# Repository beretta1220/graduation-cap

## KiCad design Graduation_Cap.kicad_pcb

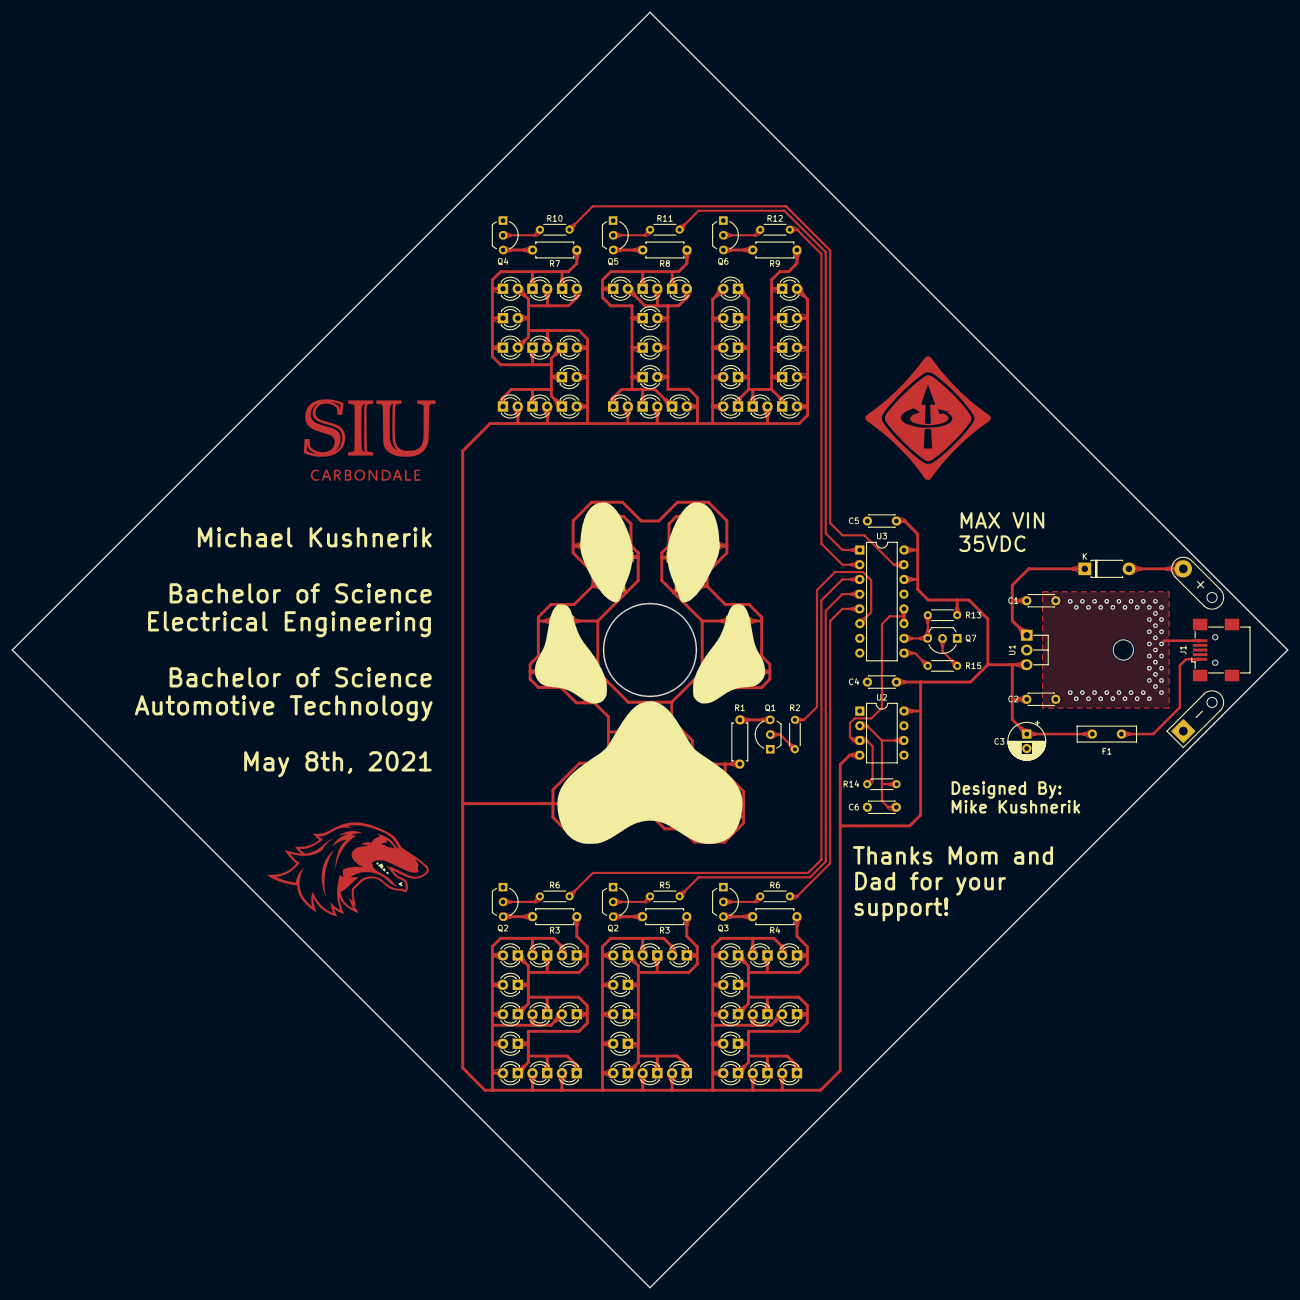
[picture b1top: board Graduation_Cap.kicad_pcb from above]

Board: 2 copper layers, 220.0 x 220.0 mm, 129 parts (0 on the bottom side), 37 nets.

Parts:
C1, C2, C4, C5, C6: 0.1uF; C_Disc_D4.3mm_W1.9mm_P5.00mm
C3: 10uF; CP_Radial_D6.3mm_P2.50mm
D1: P1; LED_D3.0mm
D2: P2; LED_D3.0mm
D3: P3; LED_D3.0mm
D4: P4; LED_D3.0mm
D5: P5; LED_D3.0mm
D6: P6; LED_D3.0mm
D7: P7; LED_D3.0mm
D8: P8; LED_D3.0mm
D9: P9; LED_D3.0mm
D10: P10; LED_D3.0mm
D11: P11; LED_D3.0mm
D12: P12; LED_D3.0mm
D13: P13; LED_D3.0mm
D14: P14; LED_D3.0mm
D15: P15; LED_D3.0mm
D16: P16; LED_D3.0mm
D17: P17; LED_D3.0mm
D18: P18; LED_D3.0mm
D19: P19; LED_D3.0mm
D20: P20; LED_D3.0mm
D21: P21; LED_D3.0mm
D22: P22; LED_D3.0mm
D23: P23; LED_D3.0mm
D24: P24; LED_D3.0mm
D25: P25; LED_D3.0mm
D26: P26; LED_D3.0mm
D27: P27; LED_D3.0mm
D28: P28; LED_D3.0mm
D29, D49: S1; LED_D3.0mm
D29#2, D60: I1; LED_D3.0mm
D30, D50: S2; LED_D3.0mm
D30#2, D61: I2; LED_D3.0mm
D31, D51: S3; LED_D3.0mm
D31#2, D62: I3; LED_D3.0mm
D32, D52: S4; LED_D3.0mm
D32#2, D63: I4; LED_D3.0mm
D33, D53: S5; LED_D3.0mm
D33#2, D64: I5; LED_D3.0mm
D34, D54: S6; LED_D3.0mm
D34#2, D65: I6; LED_D3.0mm
D35, D55: S7; LED_D3.0mm
D35#2, D66: I7; LED_D3.0mm
D36, D56: S8; LED_D3.0mm
D36#2, D67: I8; LED_D3.0mm
D37, D57: S9; LED_D3.0mm
D37#2, D68: I9; LED_D3.0mm
D38, D58: S10; LED_D3.0mm
D38#2, D69: U1; LED_D3.0mm
D39, D59: S11; LED_D3.0mm
D39#2, D70: U2; LED_D3.0mm
D40, D71: U3; LED_D3.0mm
D41, D72: U4; LED_D3.0mm
D42, D73: U5; LED_D3.0mm
D43, D74: U6; LED_D3.0mm
D44, D75: U7; LED_D3.0mm
D45, D76: U8; LED_D3.0mm
D46, D77: U9; LED_D3.0mm
D47, D78: U10; LED_D3.0mm
D48, D79: U11; LED_D3.0mm
D80: 5819; D_DO-41_SOD81_P7.62mm_Horizontal
F1: 1.5A; C_Disc_D10.0mm_W2.5mm_P5.00mm
J1: USB; USB_Mini-B_Wuerth_65100516121_Horizontal
Q1, Q2, Q2#2, Q3, Q4, Q5, Q6, Q7: PN2222A; TO-92_Inline_Wide
R1, R3, R3#2, R4, R7, R8, R9: 4.7M; R_Axial_DIN0207_L6.3mm_D2.5mm_P7.62mm_Horizontal
R2, R5, R6, R6#2, R10, R11, R12: 1K; R_Axial_DIN0204_L3.6mm_D1.6mm_P5.08mm_Horizontal
R13, R15: 10K; R_Axial_DIN0204_L3.6mm_D1.6mm_P5.08mm_Horizontal
R14: 4.7M; R_Axial_DIN0204_L3.6mm_D1.6mm_P5.08mm_Horizontal
TP1: BAT+; WIRE_SR_C
TP2: BAT-; WIRE_SR_R
U1: 7805; TO-220-3_Horizontal_TabDown
U2: NE555P; DIP-8_W7.62mm
U3: 74HC595; DIP-16_W7.62mm

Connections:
+5V: C2.1, C3.1, C4.1, C5.1, D1.2 (A), D2.2 (A), D3.2 (A), D4.2 (A), D5.2 (A), D6.2 (A), D7.2 (A), D8.2 (A), D9.2 (A), D10.2 (A), D11.2 (A), D12.2 (A), D13.2 (A), D14.2 (A), D15.2 (A), D16.2 (A), D17.2 (A), D18.2 (A), D19.2 (A), D20.2 (A), D21.2 (A), D22.2 (A), D23.2 (A), D24.2 (A), D25.2 (A), D26.2 (A), D27.2 (A), D28.2 (A), D29.2, D29#2.2 (A), D30.2, D30#2.2 (A), D31.2, D31#2.2 (A), D32.2, D32#2.2 (A), D33.2, D33#2.2 (A), D34.2, D34#2.2 (A), D35.2, D35#2.2 (A), D36.2, D36#2.2 (A), D37.2, D37#2.2 (A), D38.2, D38#2.2 (A), D39.2, D39#2.2 (A), D40.2 (A), D41.2 (A), D42.2 (A), D43.2 (A), D44.2 (A), D45.2 (A), D46.2 (A), D47.2 (A), D48.2 (A), D49.2 (A), D50.2 (A), D51.2 (A), D52.2 (A), D53.2 (A), D54.2 (A), D55.2 (A), D56.2 (A), D57.2 (A), D58.2 (A), D59.2 (A), D60.2 (A), D61.2 (A), D62.2 (A), D63.2 (A), D64.2 (A), D65.2 (A), D66.2 (A), D67.2 (A), D68.2 (A), D69.2 (A), D70.2 (A), D71.2 (A), D72.2 (A), D73.2 (A), D74.2 (A), D75.2 (A), D76.2 (A), D77.2 (A), D78.2 (A), D79.2 (A), F1.1, R13.1, U1.3 (OUT), U2.4 (MR), U2.8 (VCC), U3.14 (SER), U3.16 (VCC)
GND: C1.2, C2.2, C3.2, C4.2, C5.2, C6.2, J1.5 (GND), Q1.1 (E), Q2.1, Q2#2.1 (E), Q3.1 (E), Q4.1 (E), Q5.1 (E), Q6.1 (E), Q7.1 (E), TP2.1, U1.2 (GND), U2.1 (GND), U3.8 (GND), U3.13 (~OE)
unnamed: D1.1 (K), D2.1 (K), D3.1 (K), D4.1 (K), D5.1 (K), D6.1 (K), D7.1 (K), D8.1 (K), D9.1 (K), D10.1 (K), D11.1 (K), D12.1 (K), D13.1 (K), D14.1 (K), D15.1 (K), D16.1 (K), D17.1 (K), D18.1 (K), D19.1 (K), D20.1 (K), D21.1 (K), D22.1 (K), D23.1 (K), D24.1 (K), D25.1 (K), D26.1 (K), D27.1 (K), D28.1 (K), R1.1
unnamed: D29#2.1 (K), D30#2.1 (K), D31#2.1 (K), D32#2.1 (K), D33#2.1 (K), D34#2.1 (K), D35#2.1 (K), D36#2.1 (K), D37#2.1 (K), R3#2.1
unnamed: D29.1, D30.1, D31.1, D32.1, D33.1, D34.1, D35.1, D36.1, D37.1, D38.1, D39.1, R3.1
unnamed: D38#2.1 (K), D39#2.1 (K), D40.1 (K), D41.1 (K), D42.1 (K), D43.1 (K), D44.1 (K), D45.1 (K), D46.1 (K), D47.1 (K), D48.1 (K), R4.1
unnamed: D49.1 (K), D50.1 (K), D51.1 (K), D52.1 (K), D53.1 (K), D54.1 (K), D55.1 (K), D56.1 (K), D57.1 (K), D58.1 (K), D59.1 (K), R7.1
unnamed: D60.1 (K), D61.1 (K), D62.1 (K), D63.1 (K), D64.1 (K), D65.1 (K), D66.1 (K), D67.1 (K), D68.1 (K), R8.1
unnamed: D69.1 (K), D70.1 (K), D71.1 (K), D72.1 (K), D73.1 (K), D74.1 (K), D75.1 (K), D76.1 (K), D77.1 (K), D78.1 (K), D79.1 (K), R9.1
unnamed: D80.2 (A), TP1.1
unnamed: C1.1, D80.1 (K), U1.1 (IN)
unnamed: F1.2, J1.1 (VBUS)
unnamed: Q1.2 (B), R2.1
unnamed: Q1.3 (C), R1.2
unnamed: Q2#2.2 (B), R5.1
unnamed: Q2#2.3 (C), R3#2.2
unnamed: Q2.2, R6.1
unnamed: Q2.3, R3.2
unnamed: Q3.2 (B), R6#2.1
unnamed: Q3.3 (C), R4.2
unnamed: Q4.2 (B), R10.1
unnamed: Q4.3 (C), R7.2
unnamed: Q5.2 (B), R11.1
unnamed: Q5.3 (C), R8.2
unnamed: Q6.2 (B), R12.1
unnamed: Q6.3 (C), R9.2
unnamed: Q7.2 (B), R15.2
unnamed: Q7.3 (C), R13.2, U3.10 (~SRCLR)
unnamed: R14.1, U2.3 (OUT), U3.11 (SRCLK), U3.12 (RCLK)
unnamed: C6.1, R14.2, U2.2 (TRIG), U2.6 (THR)
unnamed: R10.2, U3.15 (Qa)
unnamed: R11.2, U3.1 (Qb)
unnamed: R12.2, U3.2 (Qc)
unnamed: R5.2, U3.4 (Qe)
unnamed: R6#2.2, U3.5 (Qf)
unnamed: R2.2, U3.6 (Qg)
unnamed: R15.1, U3.9 (~Qh)
